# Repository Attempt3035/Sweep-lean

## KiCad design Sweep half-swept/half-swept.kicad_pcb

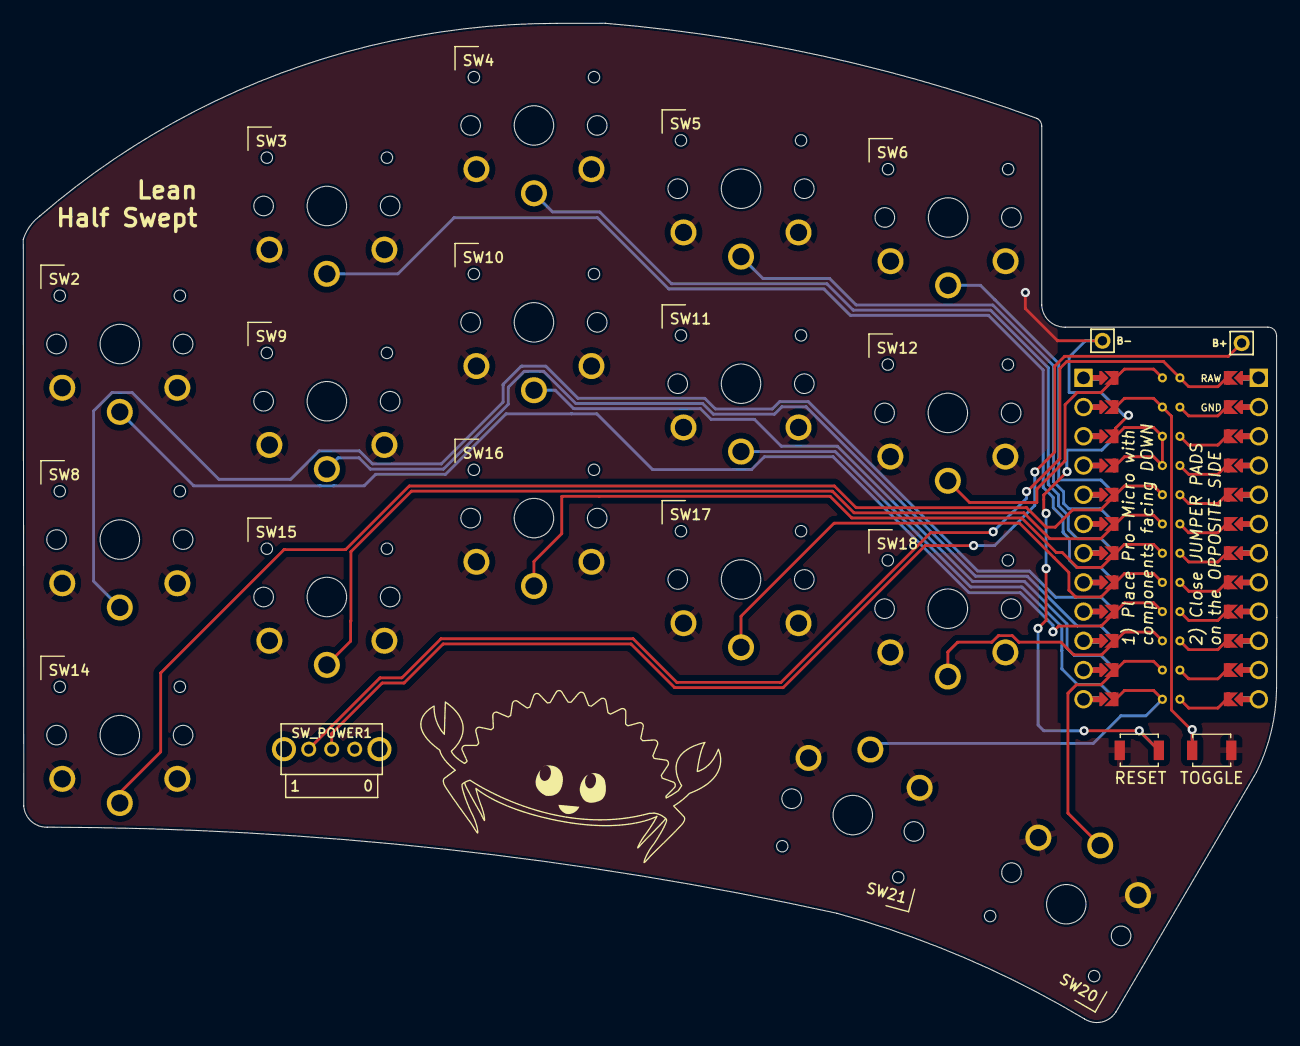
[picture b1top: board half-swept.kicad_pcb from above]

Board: 2 copper layers, 109.0 x 86.9 mm, 23 parts (0 on the bottom side), 22 nets.

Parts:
B+: MountingHole_Pad; 1pin_conn
B-: MountingHole_Pad; 1pin_conn
RSW2, RSW4: SW_Push; Tactile-Switch_SMT
SW2, SW3, SW4, SW5, SW6, SW8, SW9, SW10, SW11, SW12, SW14, SW15, SW16, SW17, SW18, SW20, SW21: SW_Push; SW_PG1350_rev_DPB
SW_POWER1: SK12D07VG4
U1: ProMicro-kbd; ProMicro_jumpers_facedown

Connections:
BT+: B+.1, SW_POWER1.COM
Switch1: SW2.1, U1.9 (D7)
Switch2: SW3.1, U1.17 (F7)
Switch3: SW4.1, U1.18 (F6)
Switch4: SW5.1, U1.19 (F5)
Switch5: SW6.1, U1.20 (F4)
Switch6: SW8.1, U1.16 (B1)
Switch7: SW9.1, U1.15 (B3)
Switch8: SW10.1, U1.14 (B2)
Switch9: SW11.1, U1.13 (B6)
Switch10: SW12.1, U1.1 (TX)
Switch11: SW14.1, U1.5 (SDA)
Switch12: SW15.1, U1.6 (SCL)
Switch13: SW16.1, U1.7 (D4)
Switch14: SW17.1, U1.8 (C6)
Switch15: SW18.1, U1.10 (E6)
Switch16: SW20.1, U1.11 (B4)
Switch17: SW21.1, U1.12 (B5)
Switch18: RSW4.1, RSW4.2, U1.2 (RX)
gnd: B-.1, RSW2.1, RSW2.2, RSW4.1, RSW4.2, SW2.2, SW3.2, SW4.2, SW5.2, SW6.2, SW8.2, SW9.2, SW10.2, SW11.2, SW12.2, SW14.2, SW15.2, SW16.2, SW17.2, SW18.2, SW20.2, SW21.2, U1.3 (GND), U1.4 (GND), U1.23 (GND)
raw: SW_POWER1.1, U1.24 (RAW)
reset: RSW2.1, RSW2.2, U1.22 (RST)

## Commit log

2025-12-14 Add Featured Forks section to README
    Added a section for featured forks with a specific example.
2026-04-08 experimental mods
